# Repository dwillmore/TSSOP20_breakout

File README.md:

# TSSOP20_breakout
A generic breakout board for TSSOP20 chips to a SIP header meant for breadboard use

New V3 coming shortly

## Features
- USB-C connection for power and/or data (proper dual 5.1K CC termination resistors)
- SO-23-5 regulator with optional stabilization capacitor
- four pin debug header with power, ground, and two additonal signals
- fully uncommitted power, ground, and USB data pins
- test pads on the back side to connect power, ground, and USB signals, etc.
- bypassable regulator (place a diode across the input to output to bypass and provide backfeed protection to the USB power
- optional component pad--useful for low speed USB for chips which lack a PHY and need a 1.5K pullup to signal bus presance
- 20x0.1" SIP header for mounting off the edge of a breadboard.  This allows the bulk of the breadboard to be use for interconnects and prototyping.

# Example boards
## CH32V203, CH32X033, and CH32V003

# BOM
This is more of a guidance than a specific BOM as it will vary with the features needed on the board and the needs of the specific chip being used.

## USB-C parts
- J4 -- USB-C USB2.0 receptacle Example: LCSC C2988369 Mfr. Part#: GT-USB-7010ASV
- R1, R2 -- USB CC1/2 termination resistors 5.1 KOhm Example: LCSC
- R3, R4 -- USB serial termination resistors 22 Ohm Example LCSC C3016215 Mfr. Part #: SCR0603F22R
- R6 -- USB speed signaling resistor 1.5 KOhm 0603 generic resistor (see other R part numbers)

## Power regulator parts
- R5 --  (not needed due to schematic error) Regulator Enable pullup resistor 10 KOhm Example: LCSC C3017715 Mfr. Part #: SCR0603J10K
- C1 -- Regulator Bypass stabilization capacitor 22 nF Example: LCSC C302021 Mfr. Part #: 0603B223K500CT
- C2, C3 -- Regulator Bypass capacitor 1 uF Example: LCSC C59782 Mfr. Part #: CL10B105KO8NNNC
- U2 -- SO23-5 regulator Example: 3.3V RT9193-33PB (needs C1), TLV743P33PDVB (does not need C1)

## SIP header and programming header
- J1, J2 -- I don't have specific part numbers for these because I have boxes of them and I just use what I need.  It's a generic 0.1"
 pin header, nothing special.

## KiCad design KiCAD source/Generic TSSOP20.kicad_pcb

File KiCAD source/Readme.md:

These are the KiCAD 7.0 source for the board V2

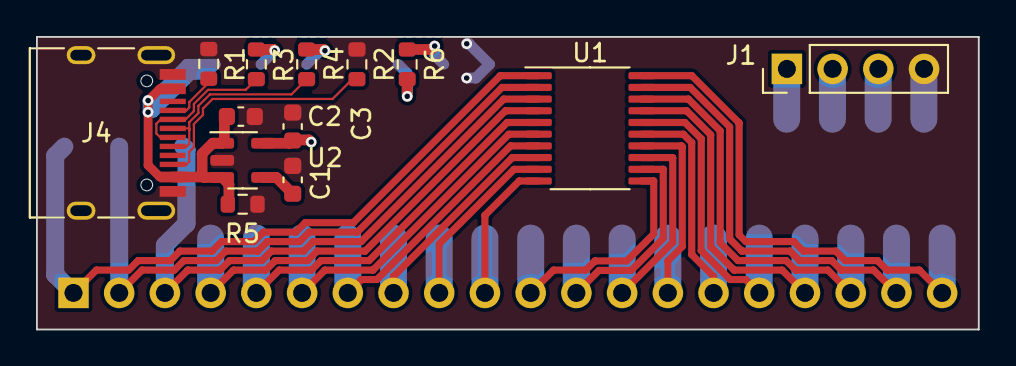
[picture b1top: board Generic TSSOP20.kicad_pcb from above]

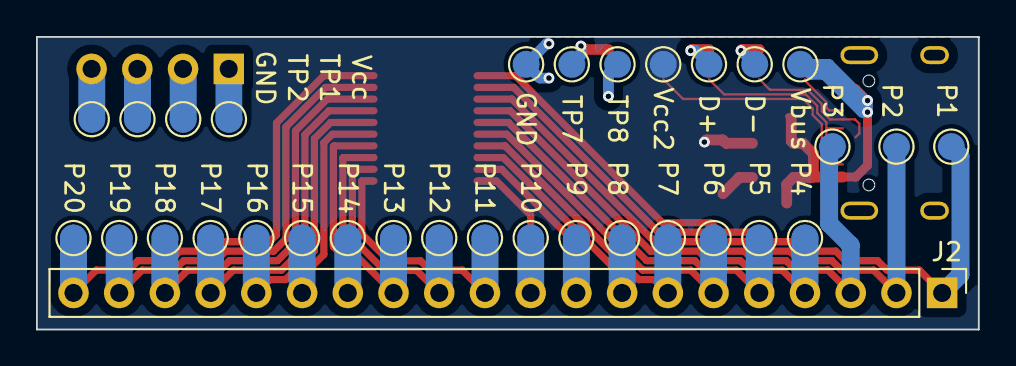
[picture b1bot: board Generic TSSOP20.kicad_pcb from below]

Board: 2 copper layers, 52.3 x 16.3 mm, 45 parts (32 on the bottom side), 35 nets.

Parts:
C1, C2, C3: C_Small; C_0603_1608Metric
D+: D+; TestPoint_Pad_D1.5mm
D-: D-; TestPoint_Pad_D1.5mm
GND: GND; TestPoint_Pad_D1.5mm
GND#2: GND; TestPoint_Pad_D1.5mm
J1: Conn_01x04_Pin; PinHeader_1x04_P2.54mm_Vertical
J2: Conn_01x20_Pin; PinHeader_1x20_P2.54mm_Vertical
J4: USB_C_Receptacle_USB2.0; USB_C_Receptacle_HRO_TYPE-C-31-M-12
P1, P2, P3, P4, P5, P6, P7, P8, P9, P10, P11, P12, P13, P15, P16, P18, P20: TestPoint_Pad_D1.5mm
P14, P17, P19: GND; TestPoint_Pad_D1.5mm
R1, R2, R3, R4, R5, R6: R_US; R_0603_1608Metric
TP1: Test/Prog1; TestPoint_Pad_D1.5mm
TP2: Test/Prog2; TestPoint_Pad_D1.5mm
TP7: USB_Pullup; TestPoint_Pad_D1.5mm
TP8: USB_PullupN; TestPoint_Pad_D1.5mm
U1: CH32V003F4P6; TSSOP-20_4.4x6.5mm_P0.65mm
U2: SOT-23-5
Vbus: Vbus; TestPoint_Pad_D1.5mm
Vcc, Vcc2: Vcc; TestPoint_Pad_D1.5mm

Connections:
/Vcc: C3.2, U2.5 (Vout), Vcc2.1
GND: C1.1, C2.1, C3.1, GND.1, GND#2.1, J1.4, J4.A1 (GND), J4.A12 (GND), J4.B1 (GND), J4.B12 (GND), J4.S1 (SHIELD), R1.2, R2.2, R5.1, U2.2 (GND)
unnamed: D+.1, R4.2
unnamed: D-.1, R3.2
unnamed: J1.1, Vcc.1
unnamed: J1.2, TP1.1
unnamed: J1.3, TP2.1
unnamed: J2.1, P1.1, U1.1 (PD4)
unnamed: J2.2, P2.1, U1.2 (PD5)
unnamed: J2.3, P3.1, U1.3 (PD6)
unnamed: J2.4, P4.1, U1.4 (PD7)
unnamed: J2.5, P5.1, U1.5 (PA1)
unnamed: J2.6, P6.1, U1.6 (PA2)
unnamed: J2.7, P7.1, U1.7 (Vss)
unnamed: J2.8, P8.1, U1.8 (PD0)
unnamed: J2.9, P9.1, U1.9 (Vdd)
unnamed: J2.10, P10.1, U1.10 (PC0)
unnamed: J2.11, P11.1, U1.11 (PC1)
unnamed: J2.12, P12.1, U1.12 (PC2)
unnamed: J2.13, P13.1, U1.13 (PC3)
unnamed: J2.14, P14.1, U1.14 (PC4)
unnamed: J2.15, P15.1, U1.15 (PC5)
unnamed: J2.16, P16.1, U1.16 (PC6)
unnamed: J2.17, P17.1, U1.17 (PC7)
unnamed: J2.18, P18.1, U1.18 (PD1)
unnamed: J2.19, P19.1, U1.19 (PD2)
unnamed: J2.20, P20.1, U1.20 (PD3)
unnamed: J4.A5 (CC1), R1.1
unnamed: J4.B5 (CC2), R2.1
unnamed: J4.A6 (D+), J4.B6 (D+), R4.1
unnamed: J4.A7 (D-), J4.B7 (D-), R3.1
unnamed: R6.1, TP7.1
unnamed: R6.2, TP8.1
unnamed: C1.2, U2.4 (BP)
unnamed: C2.2, J4.A4 (VBUS), J4.A9 (VBUS), J4.B4 (VBUS), J4.B9 (VBUS), R5.2, U2.1 (Vin), U2.3 (EN), Vbus.1

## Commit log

2024-05-24 Create Readme.md
    Initial Readme.md for the fabrication outputs.
2024-05-24 Initial set of fabrication files
2024-05-24 Update README.md
    Add board images
2024-05-24 Update README.md
    Flesh out features
2024-05-24 Update README.md
    typo
2024-05-24 Initial commit of the KiCAD source for the V2
2024-05-24 Create license.txt
    Add CERN open hardware license weakly reciprical
2024-06-03 Boards with CH32 chips on them
    This is a selection of CH32 boards with different TSSOP20 chips on them. CH32V003, CH32X033, and CHV203 are the chips on these boards.
2024-06-03 Update README.md
    Add example boards
2024-06-30 Update README.md
    Announce V3 being impending
2024-07-23 Update README.md
    Add BOM advice
2024-10-31 Update README.md
    got USB termination resistor value wrong.
